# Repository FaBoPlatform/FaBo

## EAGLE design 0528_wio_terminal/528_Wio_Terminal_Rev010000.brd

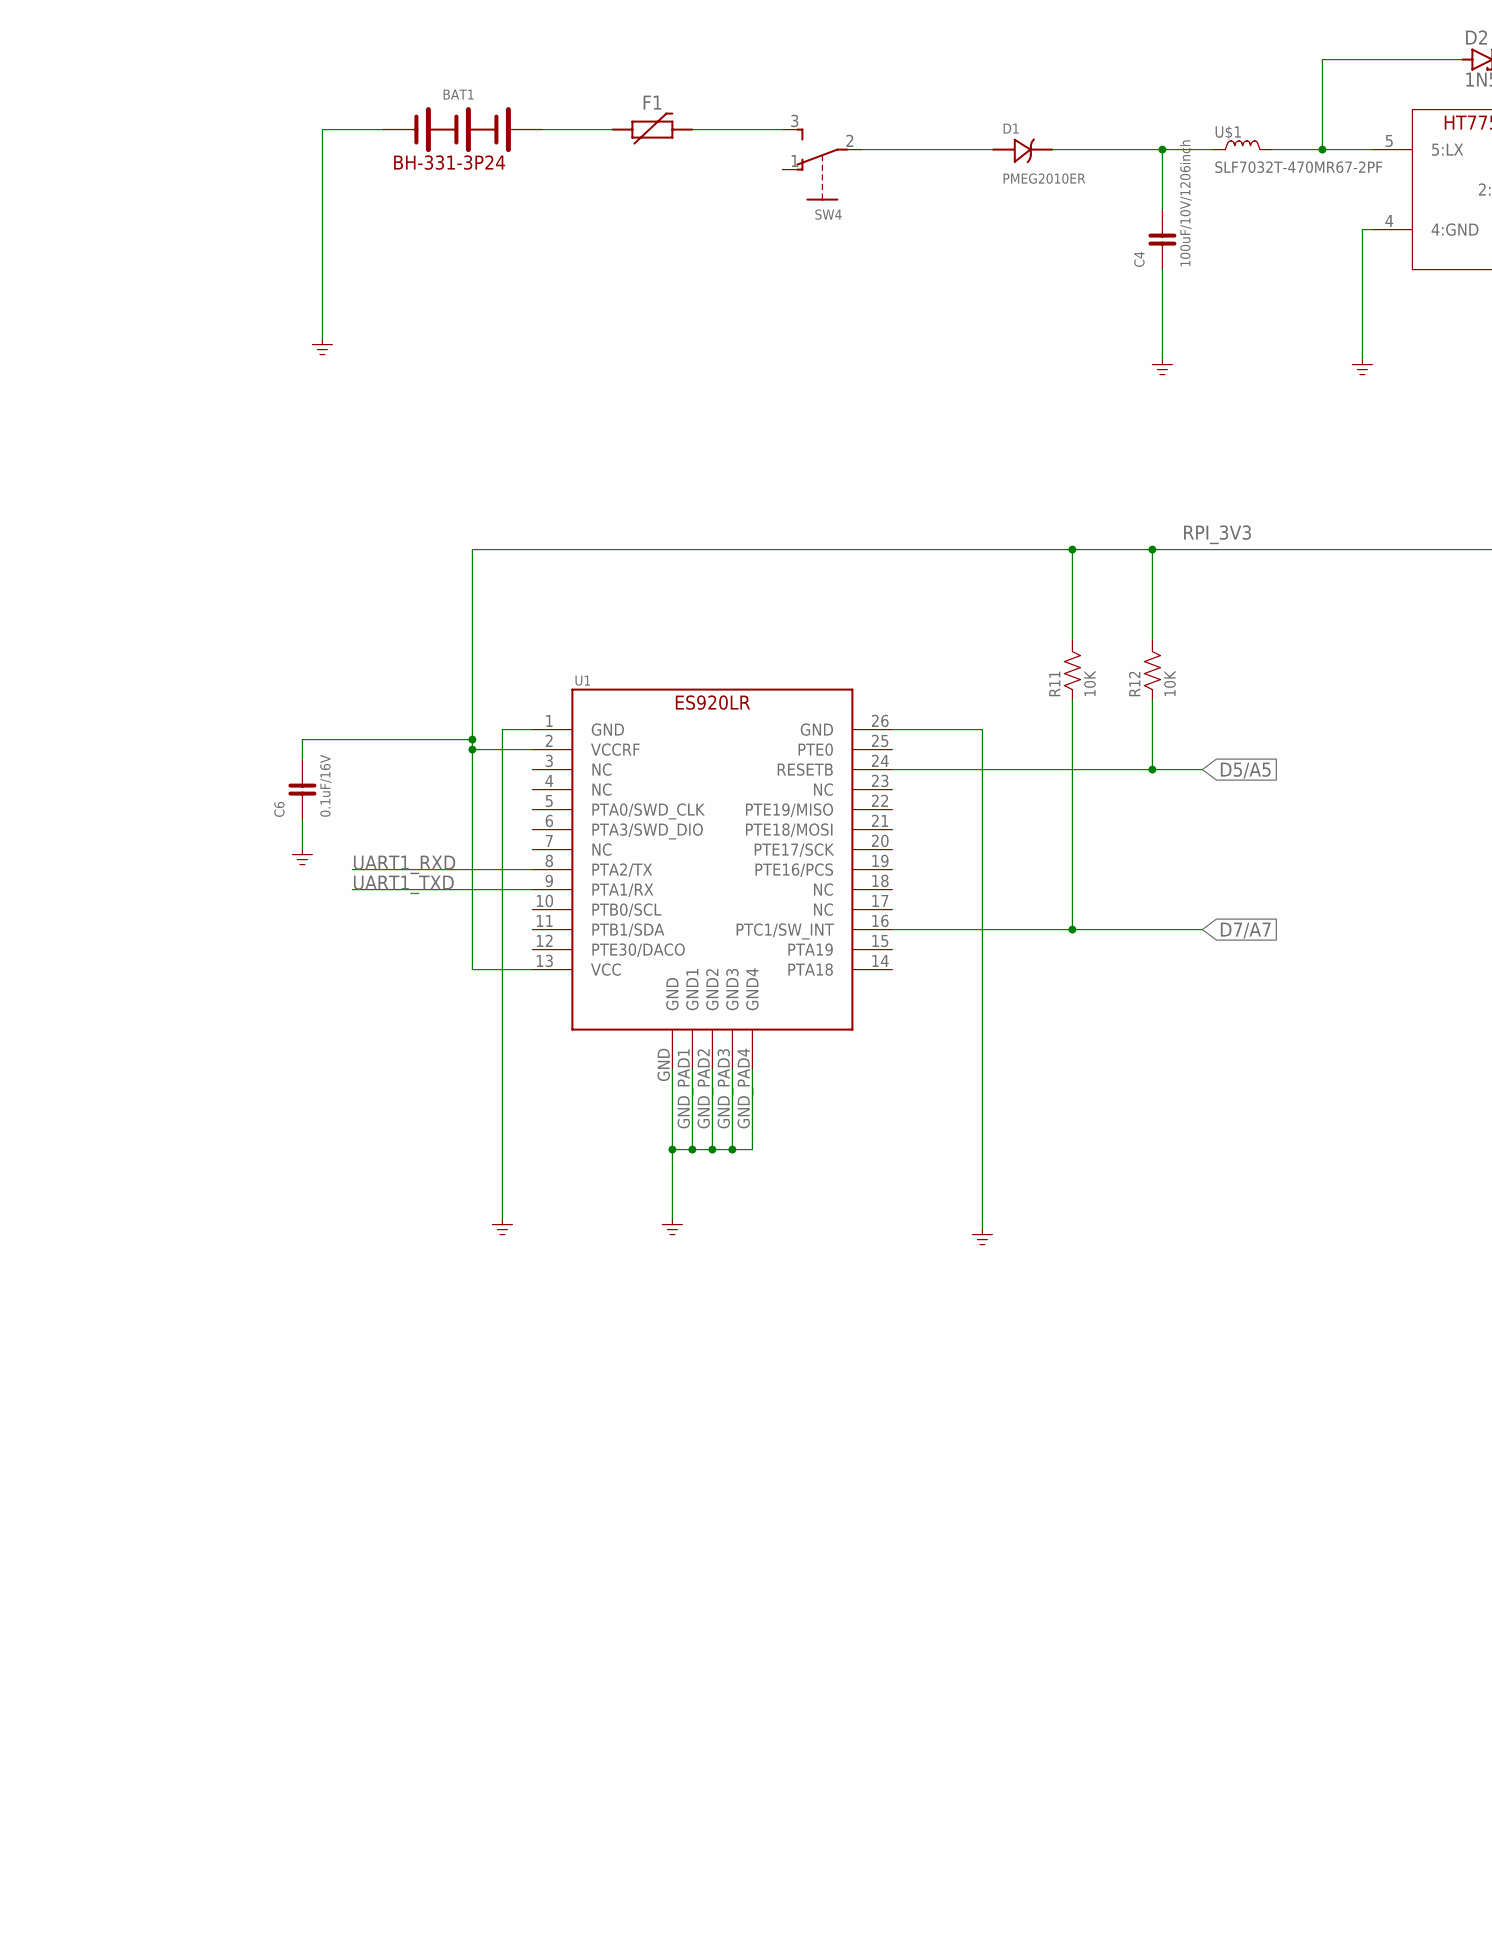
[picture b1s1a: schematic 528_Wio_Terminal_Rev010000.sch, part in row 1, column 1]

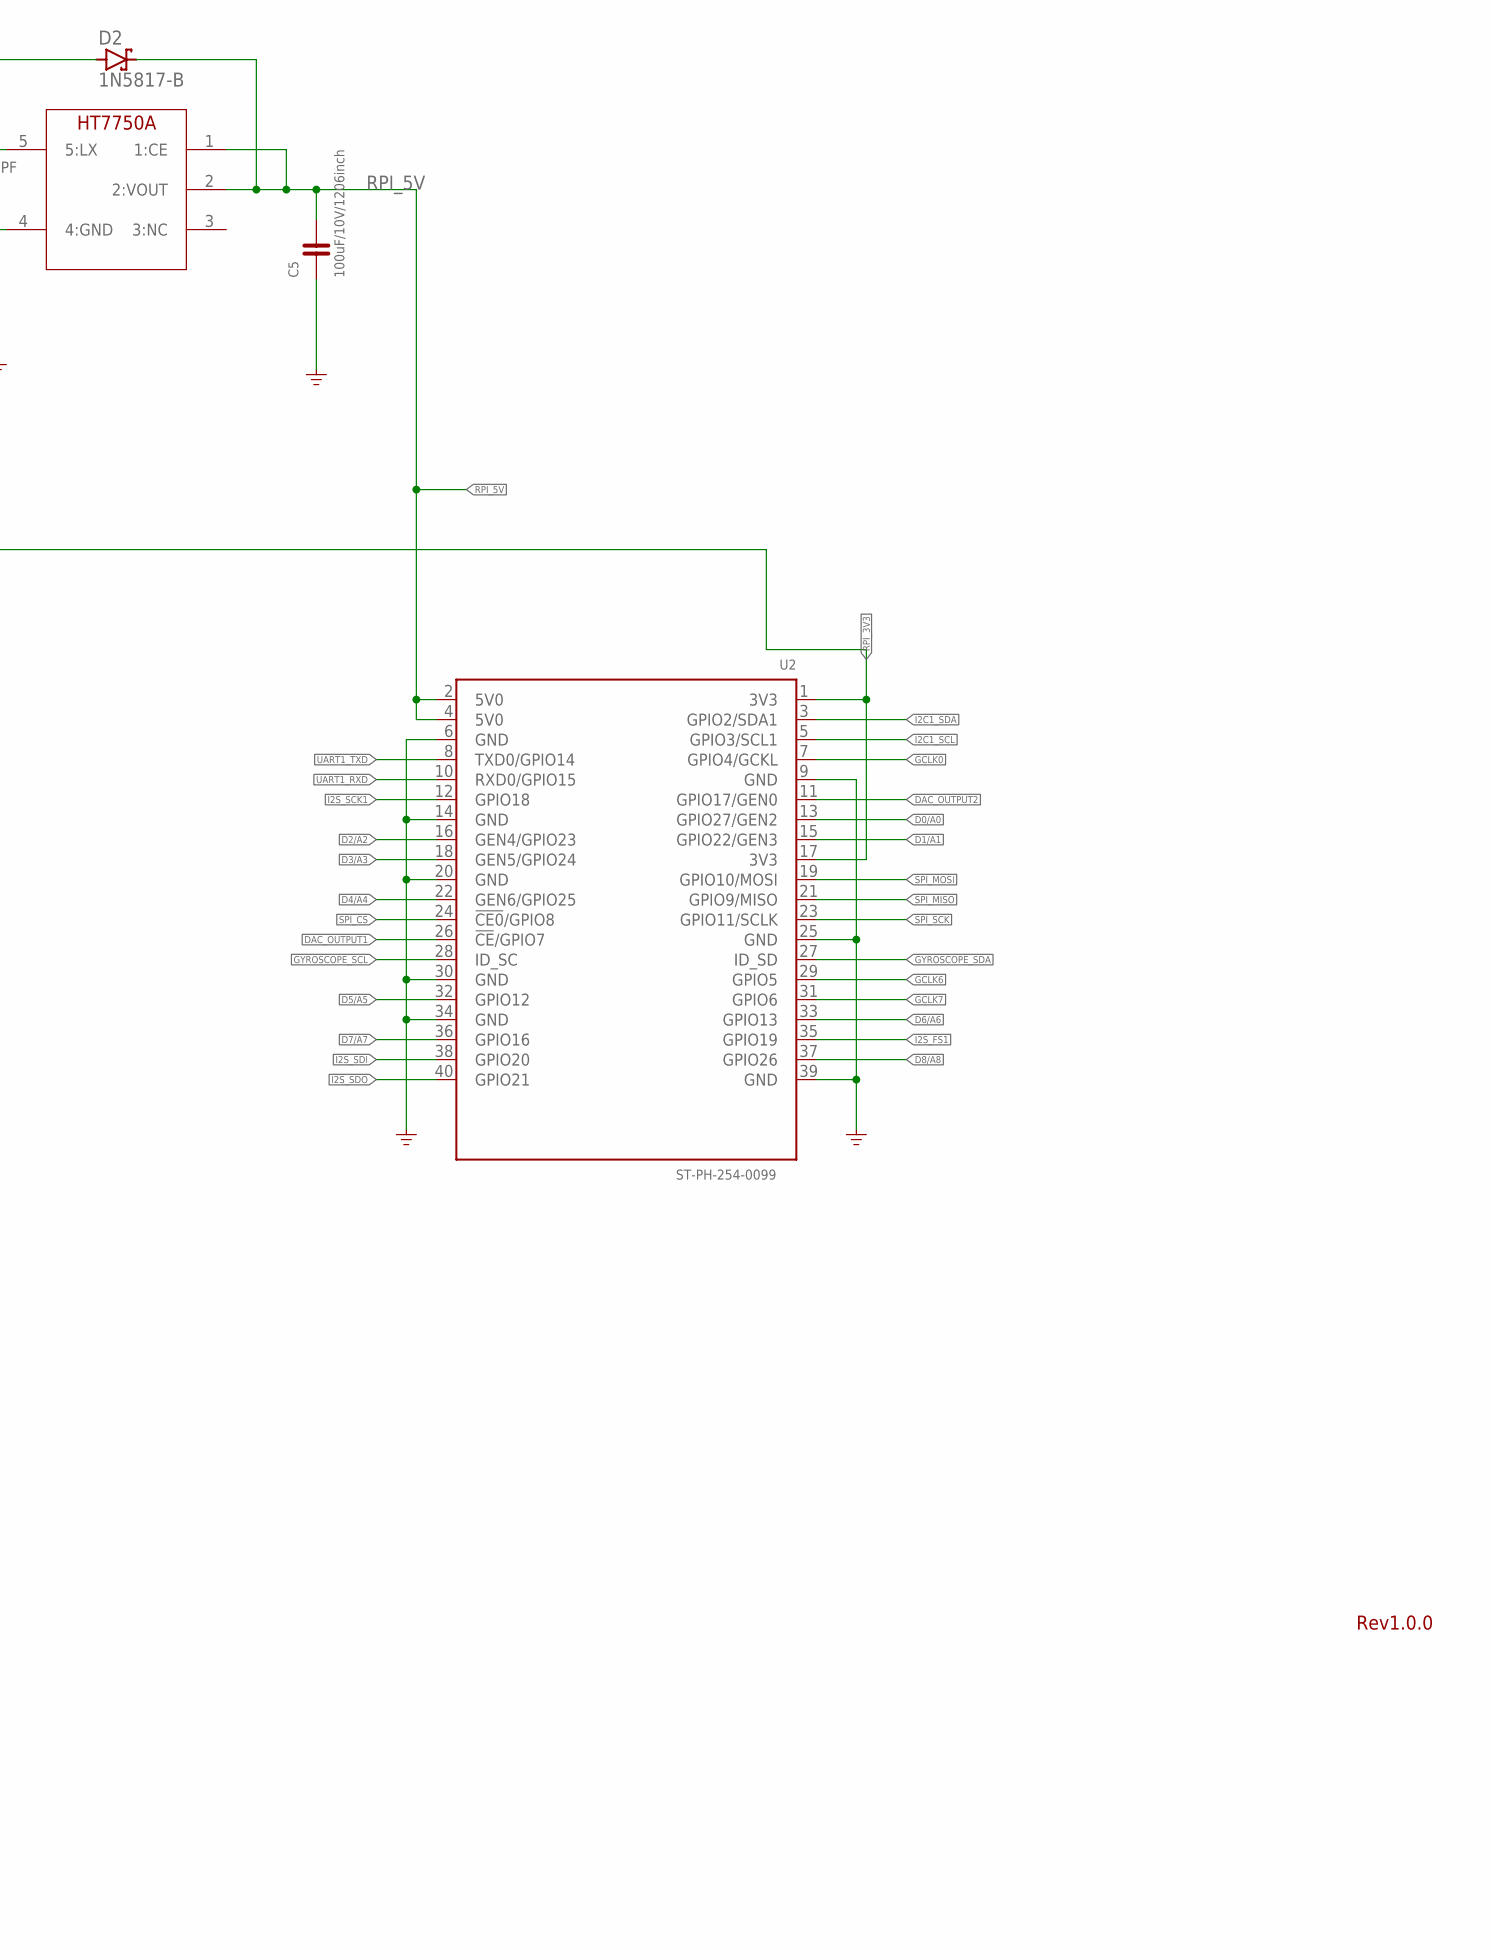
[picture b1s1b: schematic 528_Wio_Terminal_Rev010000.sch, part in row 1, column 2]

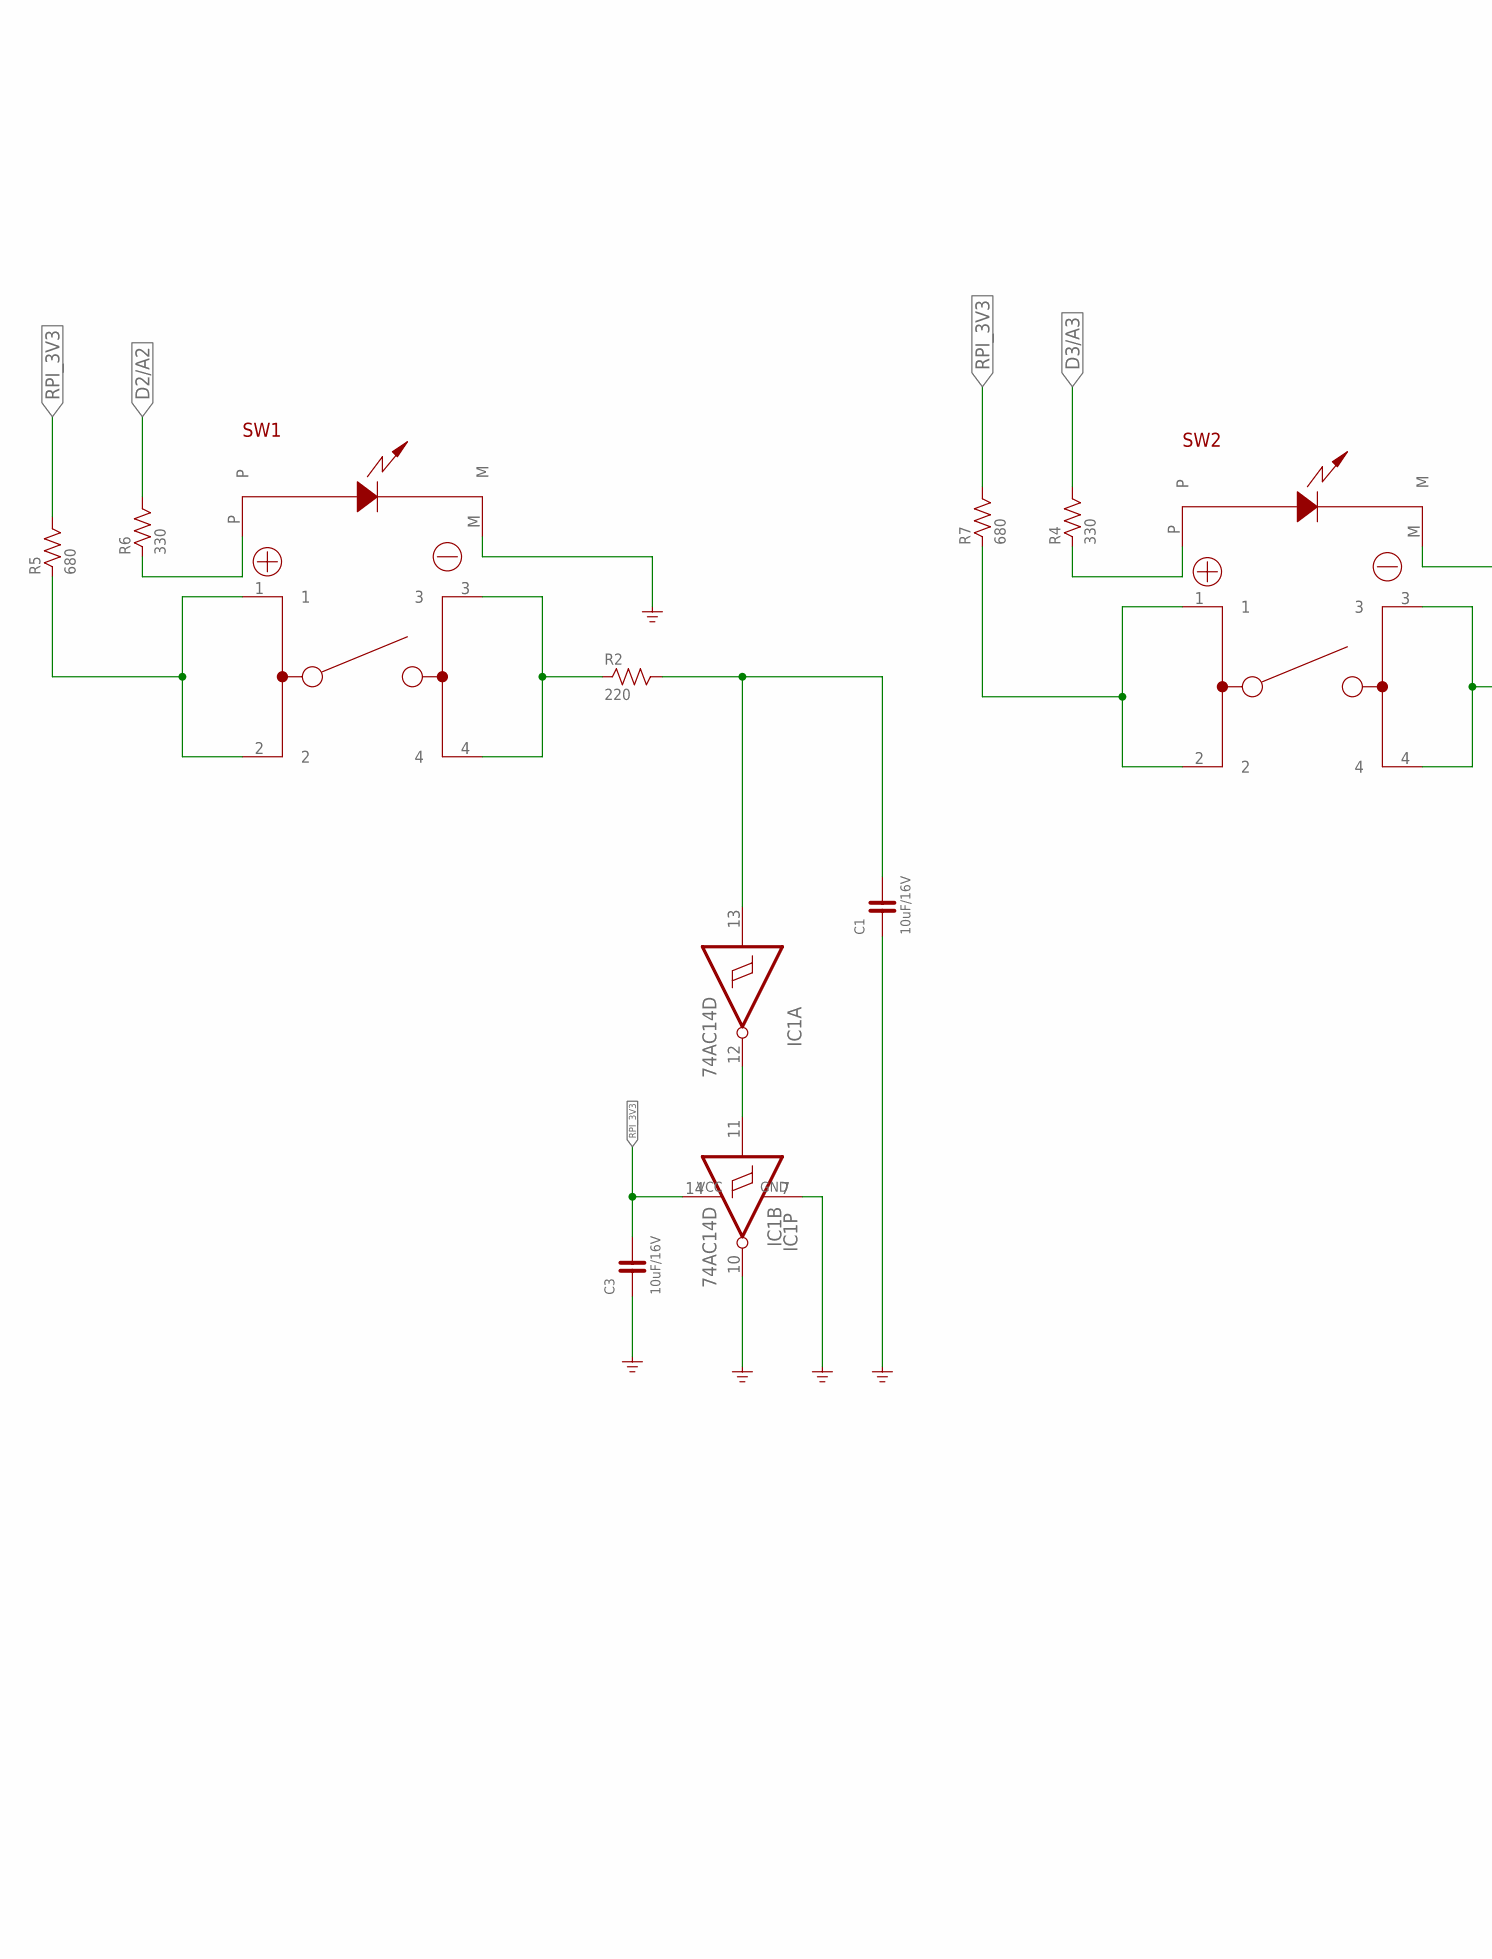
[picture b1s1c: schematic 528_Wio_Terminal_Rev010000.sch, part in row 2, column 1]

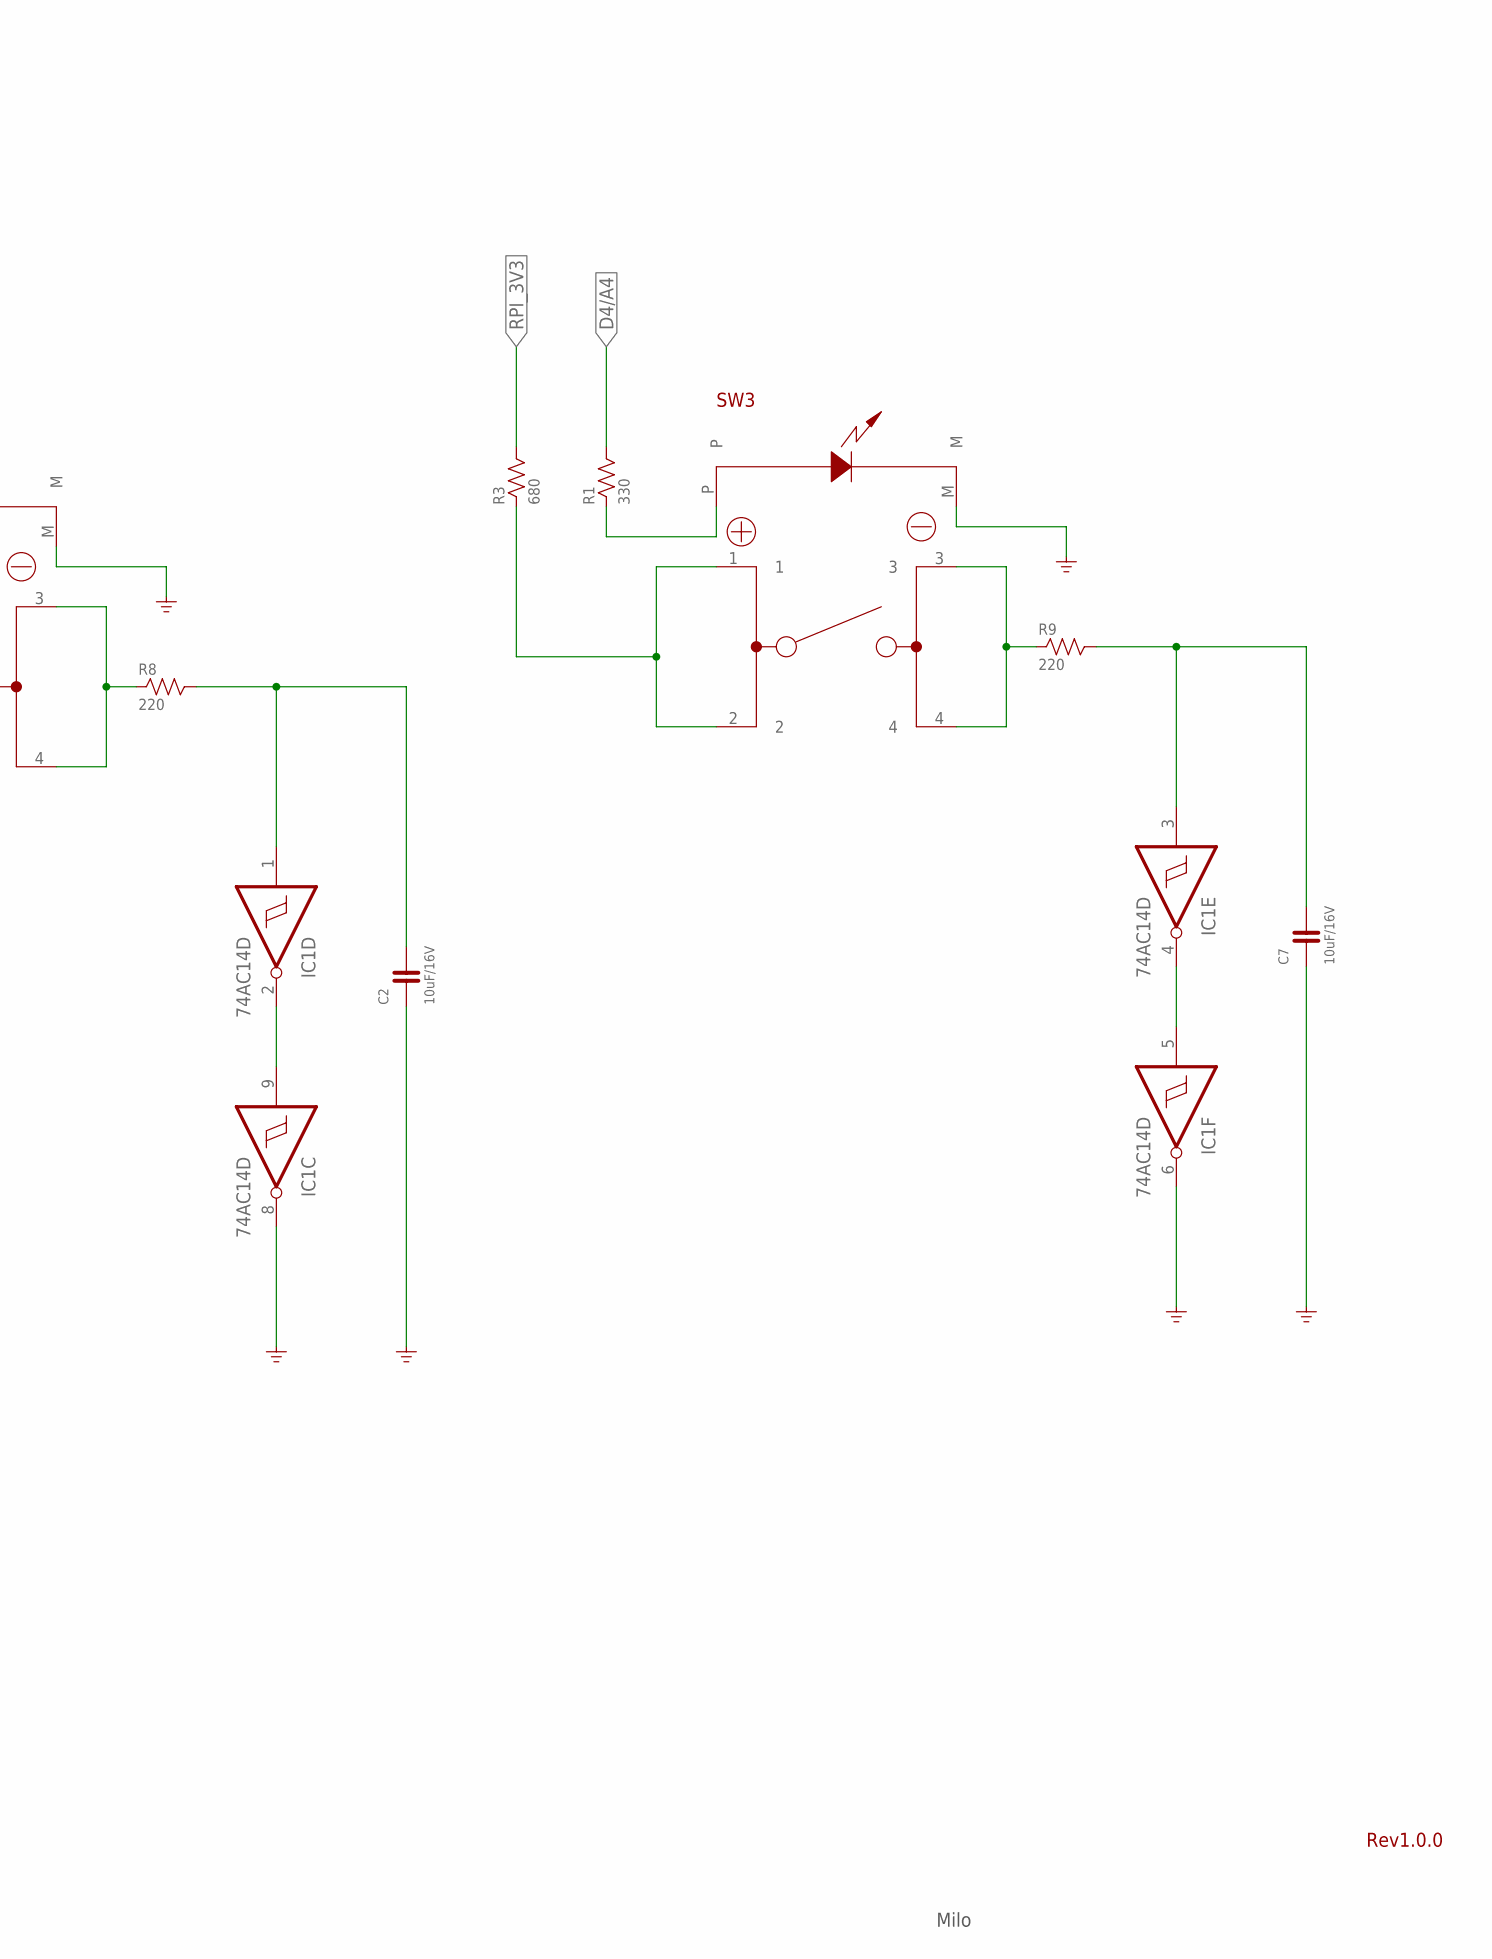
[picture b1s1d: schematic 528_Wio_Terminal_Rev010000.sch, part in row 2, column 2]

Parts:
BAT1: BH-331-3P24
C1, C2, C3, C7: 10uF/16V; 0603
C4, C5: 100uF/10V/1206inch; 1206
C6: 0.1uF/16V; 0603
D1: PMEG2010ER; SOD123W
D2: 1N5817-B; DO41-7.6
F1: POLYSWITCH1206; 1206
IC1: 74AC14D; SO14
R1, R4, R6: 330; 0603
R2, R8, R9: 220; 0603
R3, R5, R7: 680; 0603
R11, R12: 10K; 0603
SW1: LTM2-01-L2(RED); LTM2
SW2, SW3: LTM2-01-L8(YELLOW); LTM2
SW4: SLIDE-SSSS810701; SSSS810701
U1: ES920LR
U2: ST-PH-254-0099; H2X20-SMD-2.54-50.8X5MM-LONG
U$1: SLF7032T-470MR67-2PF
U$2: HT7750A; SOT-25

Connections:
D0/A0: U2.13 (GPIO27/GEN2)
D1/A1: U2.15 (GPIO22/GEN3)
D2/A2: R6.2, U2.16 (GEN4/GPIO23)
D3/A3: R4.2, U2.18 (GEN5/GPIO24)
D4/A4: R1.2, U2.22 (GEN6/GPIO25)
D5/A5: R12.1, U1.24 (RESETB), U2.32 (GPIO12)
D6/A6: U2.33 (GPIO13)
D7/A7: R11.1, U1.16 (PTC1/SW_INT), U2.36 (GPIO16)
D8/A8: U2.37 (GPIO26)
DAC_OUTPUT1: U2.26 (!CE!/GPIO7)
DAC_OUTPUT2: U2.11 (GPIO17/GEN0)
GCLK0: U2.7 (GPIO4/GCKL)
GCLK6: U2.29 (GPIO5)
GCLK7: U2.31 (GPIO6)
GND: BAT1.MINUS, C1.1, C2.1, C3.1, C4.2 (1), C5.2 (1), C6.1, C7.1, IC1.6 (O), IC1.7 (GND), IC1.8 (O), IC1.10 (O), SW1.M, SW2.M, SW3.M, U1.1 (GND), U1.26 (GND), U1.GND, U1.GND_PAD1 (GND1), U1.GND_PAD2 (GND2), U1.GND_PAD3 (GND3), U1.GND_PAD4 (GND4), U2.6 (GND), U2.9 (GND), U2.14 (GND), U2.20 (GND), U2.25 (GND), U2.30 (GND), U2.34 (GND), U2.39 (GND), U$2.4 (4:GND)
GYROSCOPE_SCL: U2.28 (ID_SC)
GYROSCOPE_SDA: U2.27 (ID_SD)
I2C1_SCL: U2.5 (GPIO3/SCL1)
I2C1_SDA: U2.3 (GPIO2/SDA1)
I2S_FS1: U2.35 (GPIO19)
I2S_SCK1: U2.12 (GPIO18)
I2S_SDI: U2.38 (GPIO20)
I2S_SDO: U2.40 (GPIO21)
unnamed: BAT1.PULS (PLUS), F1.1
unnamed: C4.1 (2), D1.1 (CATHODE), U$1.1
unnamed: D2.A, U$1.2, U$2.5 (5:LX)
unnamed: R5.1, SW1.1, SW1.2
unnamed: IC1.4 (O), IC1.5 (I)
unnamed: R2.1, SW1.3, SW1.4
unnamed: R9.1, SW3.3, SW3.4
unnamed: IC1.11 (I), IC1.12 (O)
unnamed: R6.1, SW1.P
unnamed: R3.1, SW3.1, SW3.2
unnamed: C1.2, IC1.13 (I), R2.2
unnamed: C3.2, IC1.14 (VCC)
unnamed: C7.2, IC1.3 (I), R9.2
unnamed: R1.1, SW3.P
unnamed: C2.2, IC1.1 (I), R8.2
unnamed: IC1.2 (O), IC1.9 (I)
unnamed: F1.2, SW4.3
unnamed: R8.1, SW2.3, SW2.4
unnamed: R7.1, SW2.1, SW2.2
unnamed: D1.2 (ANODE), SW4.2
unnamed: R4.1, SW2.P
RPI_3V3: C6.2, R3.2, R5.2, R7.2, R11.2, R12.2, U1.2 (VCCRF), U1.13 (VCC), U2.1 (3V3), U2.17 (3V3)
RPI_5V: C5.1 (2), D2.C, U2.2 (5V0), U2.4 (5V0), U$2.1 (1:CE), U$2.2 (2:VOUT)
SPI_CS: U2.24 (!CE0!/GPIO8)
SPI_MISO: U2.21 (GPIO9/MISO)
SPI_MOSI: U2.19 (GPIO10/MOSI)
SPI_SCK: U2.23 (GPIO11/SCLK)
UART1_RXD: U1.8 (PTA2/TX), U2.10 (RXD0/GPIO15)
UART1_TXD: U1.9 (PTA1/RX), U2.8 (TXD0/GPIO14)

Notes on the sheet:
Milo
Rev1.0.0

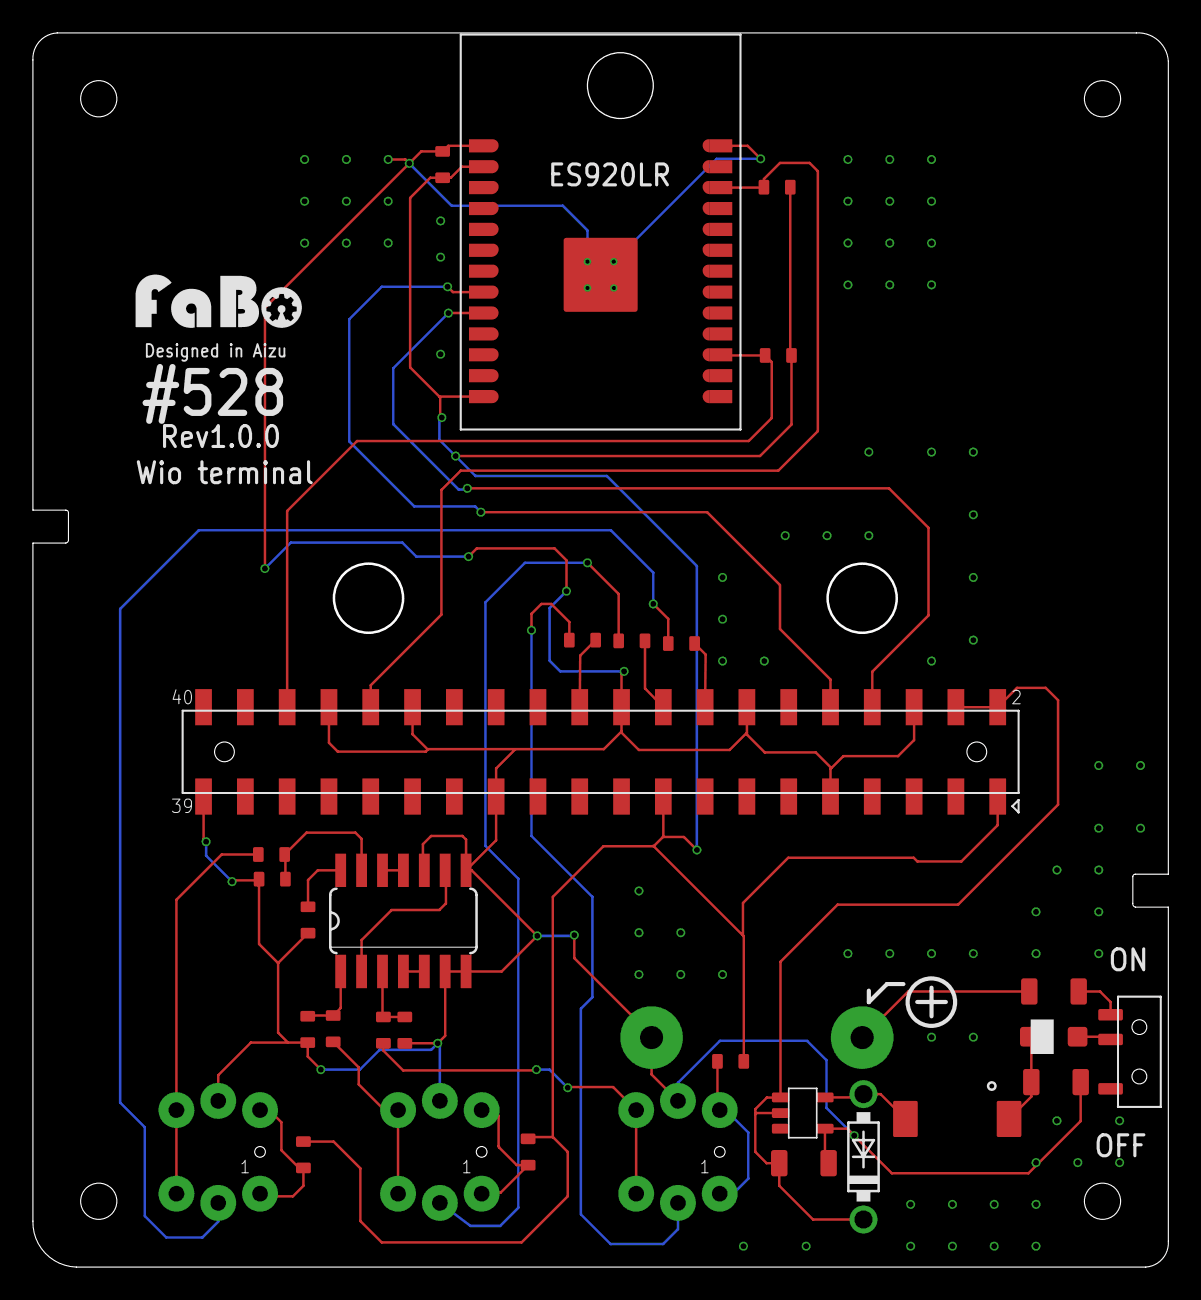
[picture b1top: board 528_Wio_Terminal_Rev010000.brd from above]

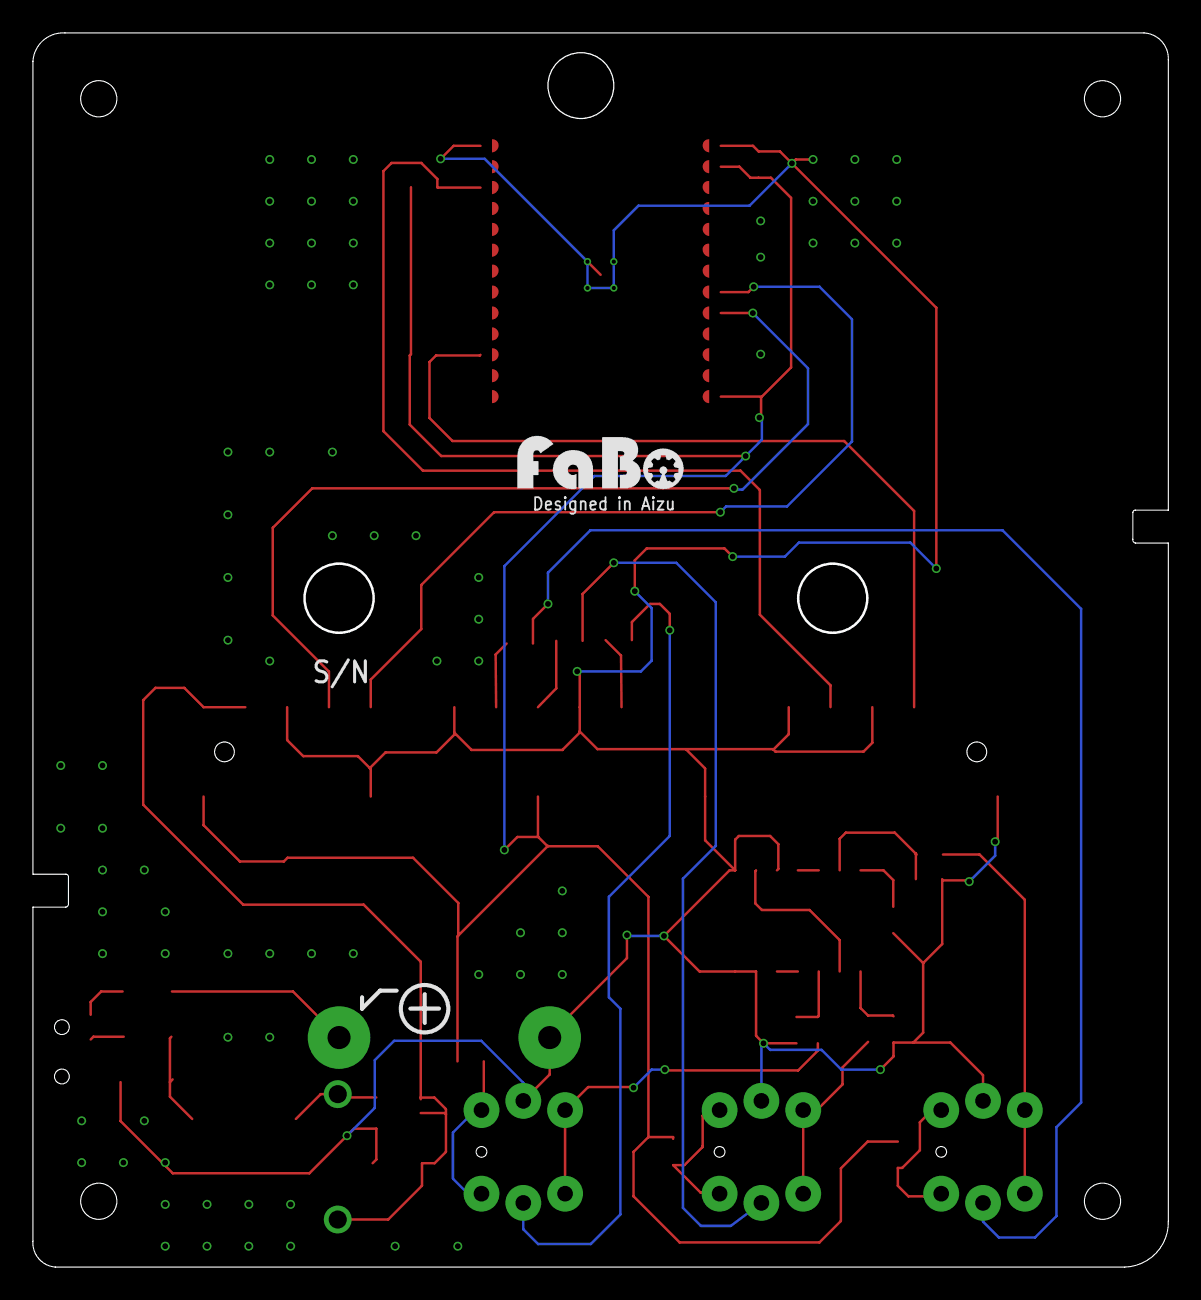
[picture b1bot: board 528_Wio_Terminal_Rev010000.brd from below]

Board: 2 copper layers, 69.0 x 75.0 mm, 33 parts (3 on the bottom side), 31 nets.

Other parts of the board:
U$3, U$4: LOGO_FABO_M

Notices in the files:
parts and their libraries:
FaBo-Switch: Released under the Creative Commons Attribution-ShareAlike 4.0 License
https://creativecommons.org/licenses/by-sa/4.0
FaBo-Symbol: Released under the Creative Commons
